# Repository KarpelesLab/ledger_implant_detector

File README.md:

# Ledger Implant Detector

> **⚠️ STATUS: PROTOTYPE, NOT VALIDATED**
>
> Rev 0.2 of the integrated board has been built (5 boards, 2026-11) and its blocks work, but it
> has a ~12 dB notch around 1.4 GHz that has to be fixed before it can run the detection rule.
> Rev 0.3 fixes the most likely cause and is generated but not built. The detection rule itself
> rests on **one genuine and one tampered Nano X**. Do not rely on this device to declare a wallet
> "clean" until it has been characterised on many more units and this banner has been removed.

| top: the cell | underside: the electronics |
|---|---|
|  |  |

A bench box for spotting **implanted antennas inside hardware wallets** (e.g. a Ledger). The target
threat is a supply-chain implant that adds a cellular (LTE) modem to the device: its antenna is a
resonant structure that a genuine unit doesn't have.

You slide the wallet into an open **TEM cell**, press a button, and read a screen and a green or red
LED. There's no VNA, no cables and no positioning skill involved. It is powered and updated over USB.

## How it detects

A TEM cell is a stripline big enough to put a wallet in: a flat metal plate (the septum) held 20 mm
above a ground plane, with tapered ramps at each end. It sets up a fairly uniform field over an
80 x 80 mm test area, so the result hardly depends on where the wallet lies.

The board sweeps a signal through the cell and measures how much comes out the other side (|S21|).
An implant antenna tuned to an LTE band absorbs energy at its resonance, which shows up as a narrow
notch in the sweep. Placement, the battery and the wallet's own electronics only change the sweep
broadly.

**The rule:** wallet sweep minus empty-cell sweep, minus a 200 MHz running median, then look in
1.0-1.45 GHz for a notch at least 0.45 dB deep and 10-60 MHz wide. If one is found, the user re-seats
the wallet and the box sweeps again; two notches within 15 MHz give red. No per-model reference
wallet is needed, if this holds up on more units.

On the NanoVNA captures of 2026-10-26 (`tools/tem_detect.py`, details in
[docs/rev02_integrated.md](docs/rev02_integrated.md#why-a-magnitude-only-sweep-is-enough)):

| | result |
|---|---|
| tampered Nano X, all placements and both orientations | 12 of 12 flagged, 0.79-1.02 dB at ~1171 MHz |
| genuine Nano X | 13 of 14 clean (at most 0.24 dB); one outlier that didn't repeat |
| re-seat and repeat | tampered 8 of 8 pairs, genuine 0 of 10 |

The implant antenna's own S11 confirms the feature: it resonates at 1156-1245 MHz depending on what
surrounds it ([data/rf/2026-11-02/notes.md](data/rf/2026-11-02/notes.md)).

The thresholds were chosen after looking at these captures, so they set a hardware target (a sweep of
800-1600 MHz in 5 MHz steps, at most 0.05 dB of noise per point) rather than proving the rule.

## What it will miss

- **Compact coil antennas**, such as Joe Grand's tampered Nano X (a hand-wound ~6 mm spiral). It is
  too small to couple to the cell's uniform field and isn't seen in simulation. The capacitive array of
  [rev 0.1](docs/rev01_capacitive.md) caught it in simulation through the shortened battery, but that
  array is not on the current board. **A green result does not rule this type out.**
- **Implants built to dodge the rule**: a low-Q antenna, or a resonance outside the band.
- **Anything unmeasured**: Stax, Nano S Plus, a genuine Flex.

## The board

Generated into `hardware/integrated/` by `tools/gen_integrated_sch.py` and
`tools/gen_integrated_pcb.py`. Full design notes, calibration, firmware security and the USB data
interface are in [docs/rev02_integrated.md](docs/rev02_integrated.md).

- **One board is both the cell floor and the electronics**, 200 x 216 mm, 4 layers
  (JLC04161H-7628). Its top copper is the cell's ground plane with the two 3 mm landing lines; every
  part is on the underside. RF crosses the board through fenced vias, so there are no cables.
- **Septum and ramps** are the fixture kit's `tem_plate` and `tem_ramp` boards, on 20 mm nylon spacers.
- **Signal chain:** ADF4351 synthesizer (35 MHz - 4.4 GHz) → 10 dB pad → cell → 6 dB pad → AD8318
  log detector → ADS1115 16-bit ADC.
- **Control:** Raspberry Pi Pico 2 module (RP2350), 2 inch ST7789 LCD, green and red LEDs, one button.
- **Hacks:** fit SMA J1/J2 and remove R1/R20 to use the cell with a NanoVNA; U.FL J5 on the
  synthesizer's second output; spare GPIO and ADC lines on J4; test points on the RF blocks.

Ordering steps: [hardware/integrated/ORDER.md](hardware/integrated/ORDER.md).

### Status

| rev | state |
|---|---|
| 0.2 | 5 boards built (JLC, 2026-11). Synthesizer, detector, ADC, LCD, LEDs and USB all work with the bring-up firmware. A ~12 dB notch near 1.4 GHz appears on both boards. Bench tests ruled out the cell, leakage and the detector's soldering, and point to long stubs on the synthesizer's RFOUTA- termination and the detector's INLO decoupling (not yet confirmed) |
| 0.3 | Generated, not built. Every ADF4351 and AD8318 support part is placed by hand at its pin, +5VA is a pour under the detector, and the router is kept out of sensitive areas. See [Rev 0.3](docs/rev02_integrated.md#rev-03-layout-fixes) |

### Firmware

`firmware/bringup` is **bring-up firmware**, not the detector: it gives raw sweeps and per-block
checks over USB serial, with no verdict and no stored reference. Build it with the Pico SDK:

```sh
cmake -S firmware/bringup -B build/bringup -G Ninja -DPICO_SDK_PATH=/path/to/pico-sdk
ninja -C build/bringup
```

Flash `build/bringup/lid_bringup.uf2` by holding BOOTSEL on the Pico while plugging it in, or send
`bootsel` to running firmware. Then use `tools/bringup.py` (Linux):

```sh
python3 tools/bringup.py cmd status               # any firmware command (try: help)
python3 tools/bringup.py sweep 1000 1450 5        # raw sweep, start/stop/step in MHz
python3 tools/bringup.py noise 1000 1450 5 -n 5   # per-point spread in dB (target <= 0.05 dB)
```

The detector firmware still has to be written: self-check, the rule, the green/red result, signed
updates and the HID interface for specialist data collection.

## How we got here

1. **Rev 0.1, capacitive array plus RF loop** ([docs/rev01_capacitive.md](docs/rev01_capacitive.md)):
   a handheld with eight capacitive electrodes and a near-field loop for a NanoVNA. Not built.
2. **Simulations** ([docs/simulation.md](docs/simulation.md)): floating antenna copper hidden behind
   the battery isn't detectable capacitively, but an RF probe sees a narrow in-band absorption that
   plain copper doesn't.
3. **First NanoVNA session** on a tampered Nano X
   ([data/rf/2026-10-18/notes.md](data/rf/2026-10-18/notes.md)): a resonance was visible, but only
   with the probe right over the antenna's feed.
4. **RF fixture kit** ([docs/fixtures.md](docs/fixtures.md), `hardware/fixtures/`): a slot line and an
   open TEM cell to remove that position dependence. On 2026-10-26 the TEM cell showed the tampered
   unit's notch at every placement ([data/rf/2026-10-26/notes.md](data/rf/2026-10-26/notes.md)).
   Crossed and coaxial large loops were simulated too, and the TEM cell stayed the practical choice.
5. **Integrated TEM cell** (rev 0.2, then 0.3): the fixture with the NanoVNA replaced by an on-board
   scalar sweep.

## Repository layout

```
hardware/
  integrated/   the integrated TEM cell (KiCad 10), fab/ has gerbers, JLC BOM/CPL, schematic PDF
  fixtures/     NanoVNA fixture kit: slot line, TEM base, septum plate, ramps
  detector/     rev 0.1 capacitive board (not built)
  lib/          project symbols and footprints
firmware/
  bringup/      rev 0.2 bring-up firmware (Pico SDK)
tools/          generators for every KiCad project, NanoVNA capture and analysis, bringup.py
sim/            electrostatic and FDTD simulations
data/rf/        NanoVNA captures with session notes
docs/           design notes, simulations, measurements, renders
```

## Regenerating

The KiCad files are generated by the scripts in `tools/`, so the design is reviewable as code. Treat
the committed `.kicad_pcb` as the source of truth: the router isn't deterministic, so regenerating
gives a different layout.

The integrated board needs KiCad 10 (its Python `pcbnew` module and `kicad-cli`), Java 17+ and
[Freerouting](https://github.com/freerouting/freerouting) 2.1.0:

```sh
cd tools
python3 gen_integrated_sch.py
FREEROUTING_JAR=/path/to/freerouting-2.1.0.jar \
    FREEROUTING_EXTRA="--gui.enabled=false --router.job_timeout=00:10:00" \
    python3 gen_integrated_pcb.py           # place, hand-route RF and support parts, autoroute, pour
python3 gen_integrated_pcb.py --outputs     # gerbers, BOM/CPL, schematic PDF, renders, DRC/ERC
```

It can leave a few connections open. Run several attempts with `LID_PCB_OUT` set to different paths
and keep one with 0 unconnected in DRC. The fixtures come from `tools/gen_fixtures.py`; the rev 0.1
board's steps are in [docs/rev01_capacitive.md](docs/rev01_capacitive.md#files-and-regenerating).

## License

Not yet chosen.

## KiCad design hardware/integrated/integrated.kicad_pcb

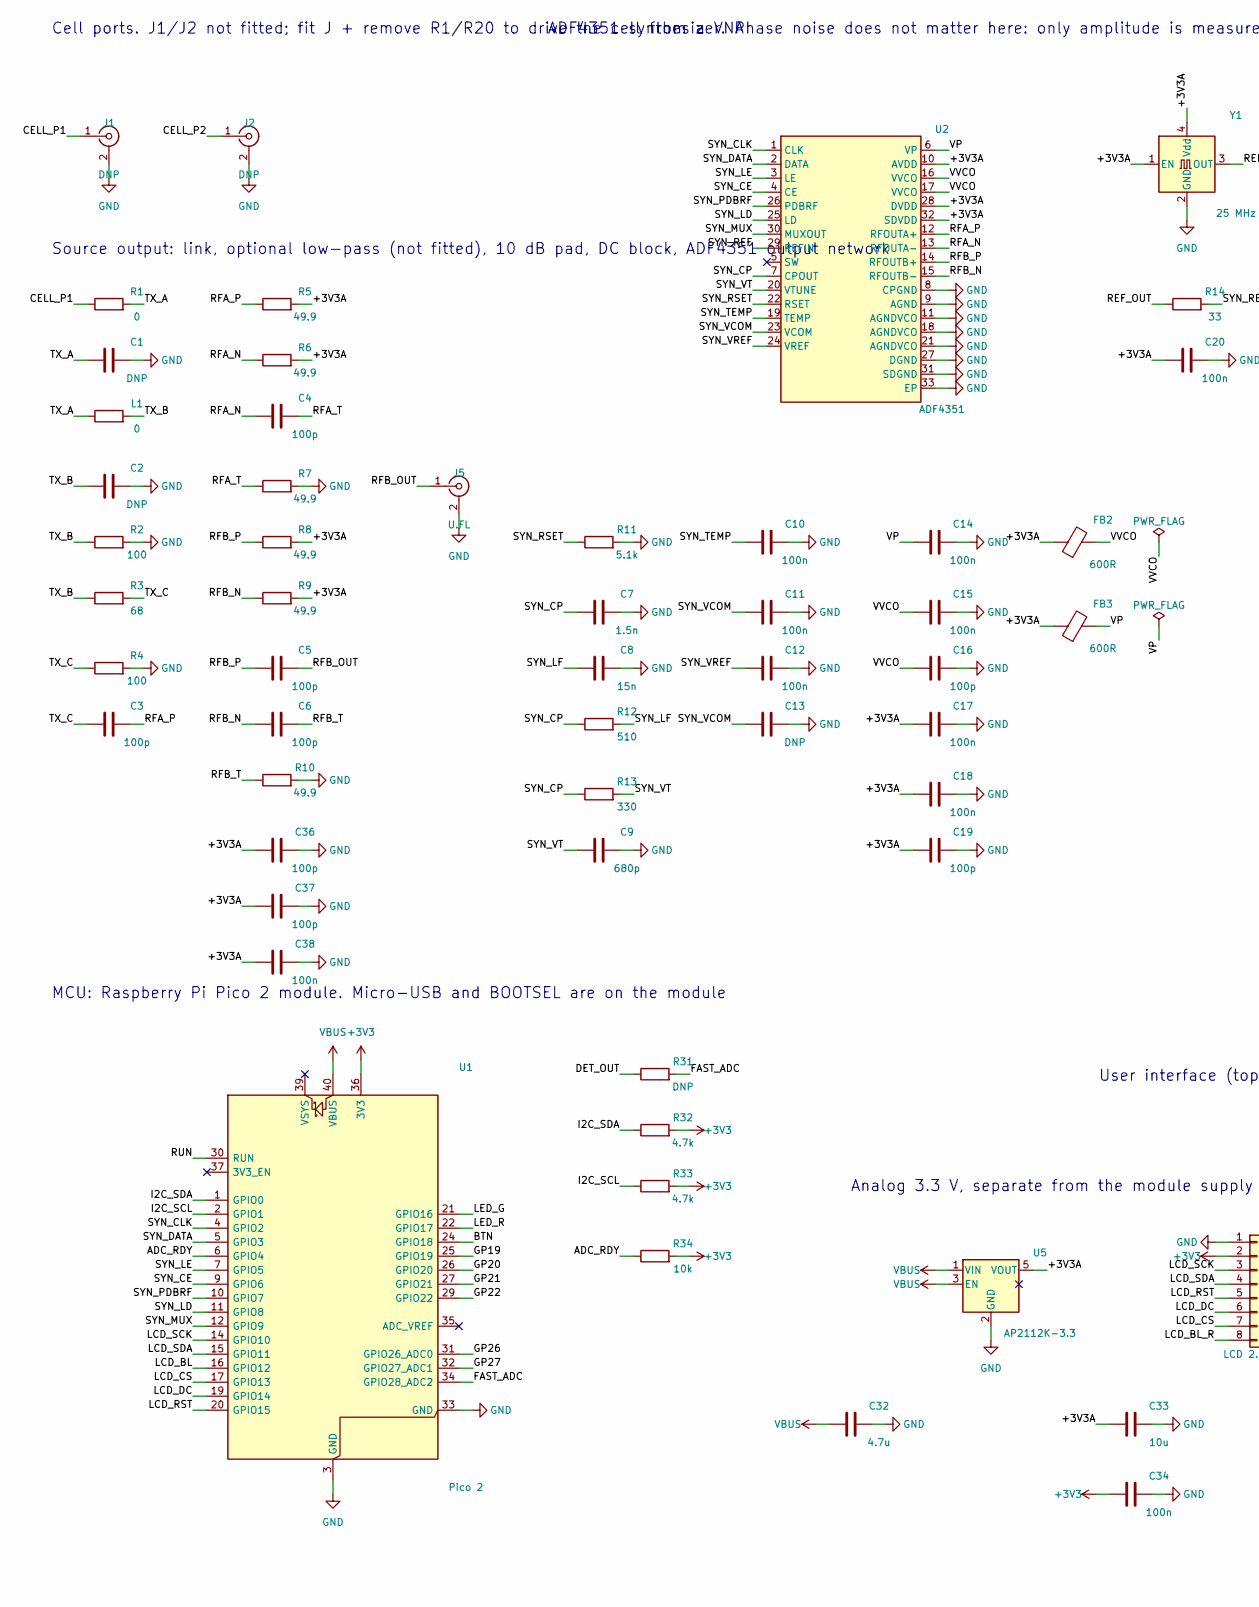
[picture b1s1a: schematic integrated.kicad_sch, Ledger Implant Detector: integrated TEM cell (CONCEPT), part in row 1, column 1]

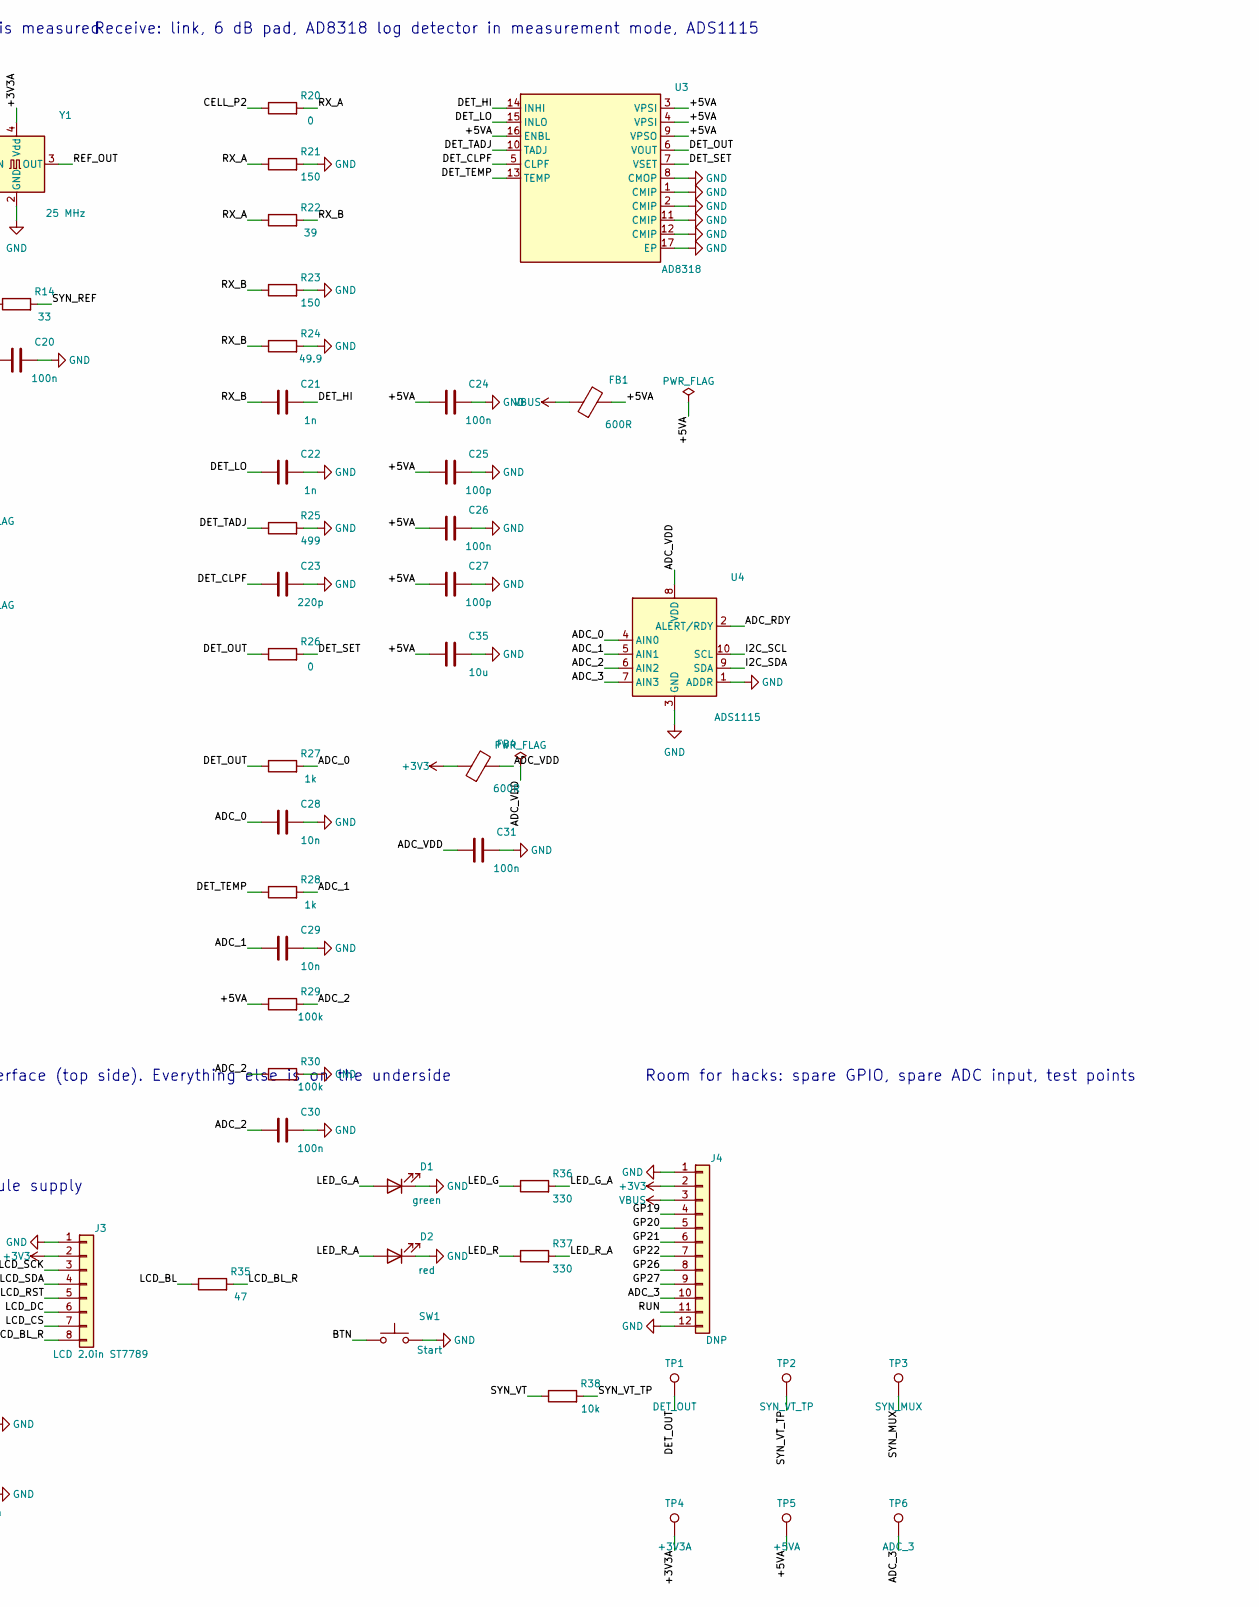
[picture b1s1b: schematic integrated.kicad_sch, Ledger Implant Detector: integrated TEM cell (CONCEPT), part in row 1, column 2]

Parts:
C1, C2, C13: DNP; C_0603_1608Metric
C3, C4, C5, C6, C16, C19, C25, C27, C36: 100p; C_0603_1608Metric
C7: 1.5n; C_0603_1608Metric
C8: 15n; C_0603_1608Metric
C9: 680p; C_0603_1608Metric
C10, C11, C12, C14, C15, C17, C18, C20, C24, C26, C30, C31, C34: 100n; C_0603_1608Metric
C21, C22: 1n; C_0603_1608Metric
C23: 220p; C_0603_1608Metric
C28, C29: 10n; C_0603_1608Metric
C32: 4.7u; C_0805_2012Metric; Voltage 10V
C33, C35: 10u; C_0805_2012Metric; Voltage 10V
C37: 100p; C_0402_1005Metric
C38: 100n; C_0402_1005Metric
D1: green; LED_D5.0mm
D2: red; LED_D5.0mm
FB1, FB2, FB3, FB4: 600R; L_0603_1608Metric
J1, J2: DNP; SMA_Samtec_SMA-J-P-H-ST-EM1_EdgeMount
J3: LCD 2.0in ST7789; PinHeader_1x08_P2.54mm_Vertical
J4: DNP; PinHeader_1x12_P2.54mm_Vertical
J5: U.FL; U.FL_Hirose_U.FL-R-SMT-1_Vertical; MPN U.FL-R-SMT-1(80); LCSC C88374
L1: 0; R_0603_1608Metric
R1, R20, R26: 0; R_0603_1608Metric
R2, R4: 100; R_0603_1608Metric
R3: 68; R_0603_1608Metric
R5, R6, R7, R8, R9, R10, R24: 49.9; R_0603_1608Metric
R11: 5.1k; R_0603_1608Metric
R12: 510; R_0603_1608Metric
R13, R36, R37: 330; R_0603_1608Metric
R14: 33; R_0603_1608Metric
R21, R23: 150; R_0603_1608Metric
R22: 39; R_0603_1608Metric
R25: 499; R_0603_1608Metric
R27, R28: 1k; R_0603_1608Metric
R29, R30: 100k; R_0603_1608Metric
R31: DNP; R_0603_1608Metric
R32, R33: 4.7k; R_0603_1608Metric
R34, R38: 10k; R_0603_1608Metric
R35: 47; R_0603_1608Metric
SW1: Start; SW_PUSH_6mm
TP1: DET_OUT; TestPoint_Pad_D1.5mm
TP2: SYN_VT_TP; TestPoint_Pad_D1.5mm
TP3: SYN_MUX; TestPoint_Pad_D1.5mm
TP4: +3V3A; TestPoint_Pad_D1.5mm
TP5: +5VA; TestPoint_Pad_D1.5mm
TP6: ADC_3; TestPoint_Pad_D1.5mm
U1: Pico 2; RaspberryPi_Pico_Common_THT; MPN SC1631
U2: ADF4351; QFN-32-1EP_5x5mm_P0.5mm_EP3.45x3.45mm; MPN ADF4351BCPZ
U3: AD8318; Analog_LFCSP-16-1EP_4x4mm_P0.65mm_EP2.35x2.35mm; MPN AD8318ACPZ-REEL7
U4: ADS1115; TSSOP-10_3x3mm_P0.5mm; MPN ADS1115IDGSR
U5: AP2112K-3.3; SOT-23-5; MPN AP2112K-3.3TRG1
Y1: 25 MHz; Oscillator_SMD_Abracon_ASE-4Pin_3.2x2.5mm; MPN OT322525MJBA4SL; LCSC C669088

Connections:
+3V3: C34.1, FB4.1, J3.2, J4.2, R32.2, R33.2, R34.2, U1.36 (3V3)
/+3V3A: C17.1, C18.1, C19.1, C20.1, C33.1, C36.1, C37.1, C38.1, FB2.1, FB3.1, R5.2, R6.2, R8.2, R9.2, TP4.1, U2.10 (AVDD), U2.28 (DVDD), U2.32 (SDVDD), U5.5 (VOUT), Y1.1 (EN), Y1.4 (Vdd)
/ADC_0: C28.1, R27.2, U4.4 (AIN0)
/ADC_1: C29.1, R28.2, U4.5 (AIN1)
/ADC_2: C30.1, R29.2, R30.1, U4.6 (AIN2)
/ADC_3: J4.10, TP6.1, U4.7 (AIN3)
/ADC_RDY: R34.1, U1.6 (GPIO4), U4.2 (ALERT/RDY)
/BTN: SW1.1, U1.24 (GPIO18)
/CELL_P1: J1.1 (In), R1.1
/CELL_P2: J2.1 (In), R20.1
/DET_CLPF: C23.1, U3.5 (CLPF)
/DET_HI: C21.2, U3.14 (INHI)
/DET_LO: C22.1, U3.15 (INLO)
/DET_OUT: R26.1, R27.1, R31.1, TP1.1, U3.6 (VOUT)
/DET_SET: R26.2, U3.7 (VSET)
/DET_TADJ: R25.1, U3.10 (TADJ)
/DET_TEMP: R28.1, U3.13 (TEMP)
/FAST_ADC: R31.2, U1.34 (GPIO28_ADC2)
/GP19: J4.4, U1.25 (GPIO19)
/GP20: J4.5, U1.26 (GPIO20)
/GP21: J4.6, U1.27 (GPIO21)
/GP22: J4.7, U1.29 (GPIO22)
/GP26: J4.8, U1.31 (GPIO26_ADC0)
/GP27: J4.9, U1.32 (GPIO27_ADC1)
/I2C_SCL: R33.1, U1.2 (GPIO1), U4.10 (SCL)
/I2C_SDA: R32.1, U1.1 (GPIO0), U4.9 (SDA)
/LCD_BL: R35.1, U1.16 (GPIO12)
/LCD_BL_R: J3.8, R35.2
/LCD_CS: J3.7, U1.17 (GPIO13)
/LCD_DC: J3.6, U1.19 (GPIO14)
/LCD_RST: J3.5, U1.20 (GPIO15)
/LCD_SCK: J3.3, U1.14 (GPIO10)
/LCD_SDA: J3.4, U1.15 (GPIO11)
/LED_G: R36.1, U1.21 (GPIO16)
/LED_G_A: D1.2 (A), R36.2
/LED_R: R37.1, U1.22 (GPIO17)
/LED_R_A: D2.2 (A), R37.2
/REF_OUT: R14.1, Y1.3 (OUT)
/RFA_N: C4.1, R6.1, U2.13 (RFOUTA-)
/RFA_P: C3.2, R5.1, U2.12 (RFOUTA+)
/RFA_T: C4.2, R7.1
/RFB_N: C6.1, R9.1, U2.15 (RFOUTB-)
/RFB_OUT: C5.2, J5.1 (In)
/RFB_P: C5.1, R8.1, U2.14 (RFOUTB+)
/RFB_T: C6.2, R10.1
/RUN: J4.11, U1.30 (RUN)
/RX_A: R20.2, R21.1, R22.1
/RX_B: C21.1, R22.2, R23.1, R24.1
/SYN_CE: U1.9 (GPIO6), U2.4 (CE)
/SYN_CLK: U1.4 (GPIO2), U2.1 (CLK)
/SYN_CP: C7.1, R12.1, R13.1, U2.7 (CPOUT)
/SYN_DATA: U1.5 (GPIO3), U2.2 (DATA)
/SYN_LD: U1.11 (GPIO8), U2.25 (LD)
/SYN_LE: U1.7 (GPIO5), U2.3 (LE)
/SYN_LF: C8.1, R12.2
/SYN_MUX: TP3.1, U1.12 (GPIO9), U2.30 (MUXOUT)
/SYN_PDBRF: U1.10 (GPIO7), U2.26 (PDBRF)
/SYN_REF: R14.2, U2.29 (REFIN)
/SYN_RSET: R11.1, U2.22 (RSET)
/SYN_TEMP: C10.1, U2.19 (TEMP)
/SYN_VCOM: C11.1, C13.1, U2.23 (VCOM)
/SYN_VREF: C12.1, U2.24 (VREF)
/SYN_VT: C9.1, R13.2, R38.1, U2.20 (VTUNE)
/SYN_VT_TP: R38.2, TP2.1
/TX_A: C1.1, L1.1, R1.2
/TX_B: C2.1, L1.2, R2.1, R3.1
/TX_C: C3.1, R3.2, R4.1
GND: C1.2, C2.2, C7.2, C8.2, C9.2, C10.2, C11.2, C12.2, C13.2, C14.2, C15.2, C16.2, C17.2, C18.2, C19.2, C20.2, C22.2, C23.2, C24.2, C25.2, C26.2, C27.2, C28.2, C29.2, C30.2, C31.2, C32.2, C33.2, C34.2, C35.2, C36.2, C37.2, C38.2, D1.1 (K), D2.1 (K), J1.2 (Ext), J2.2 (Ext), J3.1, J4.1, J4.12, J5.2 (Ext), R2.2, R4.2, R7.2, R10.2, R11.2, R21.2, R23.2, R24.2, R25.2, R30.2, SW1.2, U1.3 (GND), U1.8 (GND), U1.13 (GND), U1.18 (GND), U1.23 (GND), U1.28 (GND), U1.33 (AGND), U1.38 (GND), U2.8 (CPGND), U2.9 (AGND), U2.11 (AGNDVCO), U2.18 (AGNDVCO), U2.21 (AGNDVCO), U2.27 (DGND), U2.31 (SDGND), U2.33 (EP), U3.1 (CMIP), U3.2 (CMIP), U3.8 (CMOP), U3.11 (CMIP), U3.12 (CMIP), U3.17 (EP), U4.1 (ADDR), U4.3 (GND), U5.2 (GND), Y1.2 (GND)
VBUS: C32.1, FB1.1, J4.3, U1.40 (VBUS), U5.1 (VIN), U5.3 (EN)

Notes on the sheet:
Cell ports. J1/J2 not fitted; fit J + remove R1/R20 to drive the cell from a VNA
Source output: link, optional low-pass (not fitted), 10 dB pad, DC block, ADF4351 output network
ADF4351 synthesizer. Phase noise does not matter here: only amplitude is measured
Receive: link, 6 dB pad, AD8318 log detector in measurement mode, ADS1115
MCU: Raspberry Pi Pico 2 module. Micro-USB and BOOTSEL are on the module
Analog 3.3 V, separate from the module supply
User interface (top side). Everything else is on the underside
Room for hacks: spare GPIO, spare ADC input, test points

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
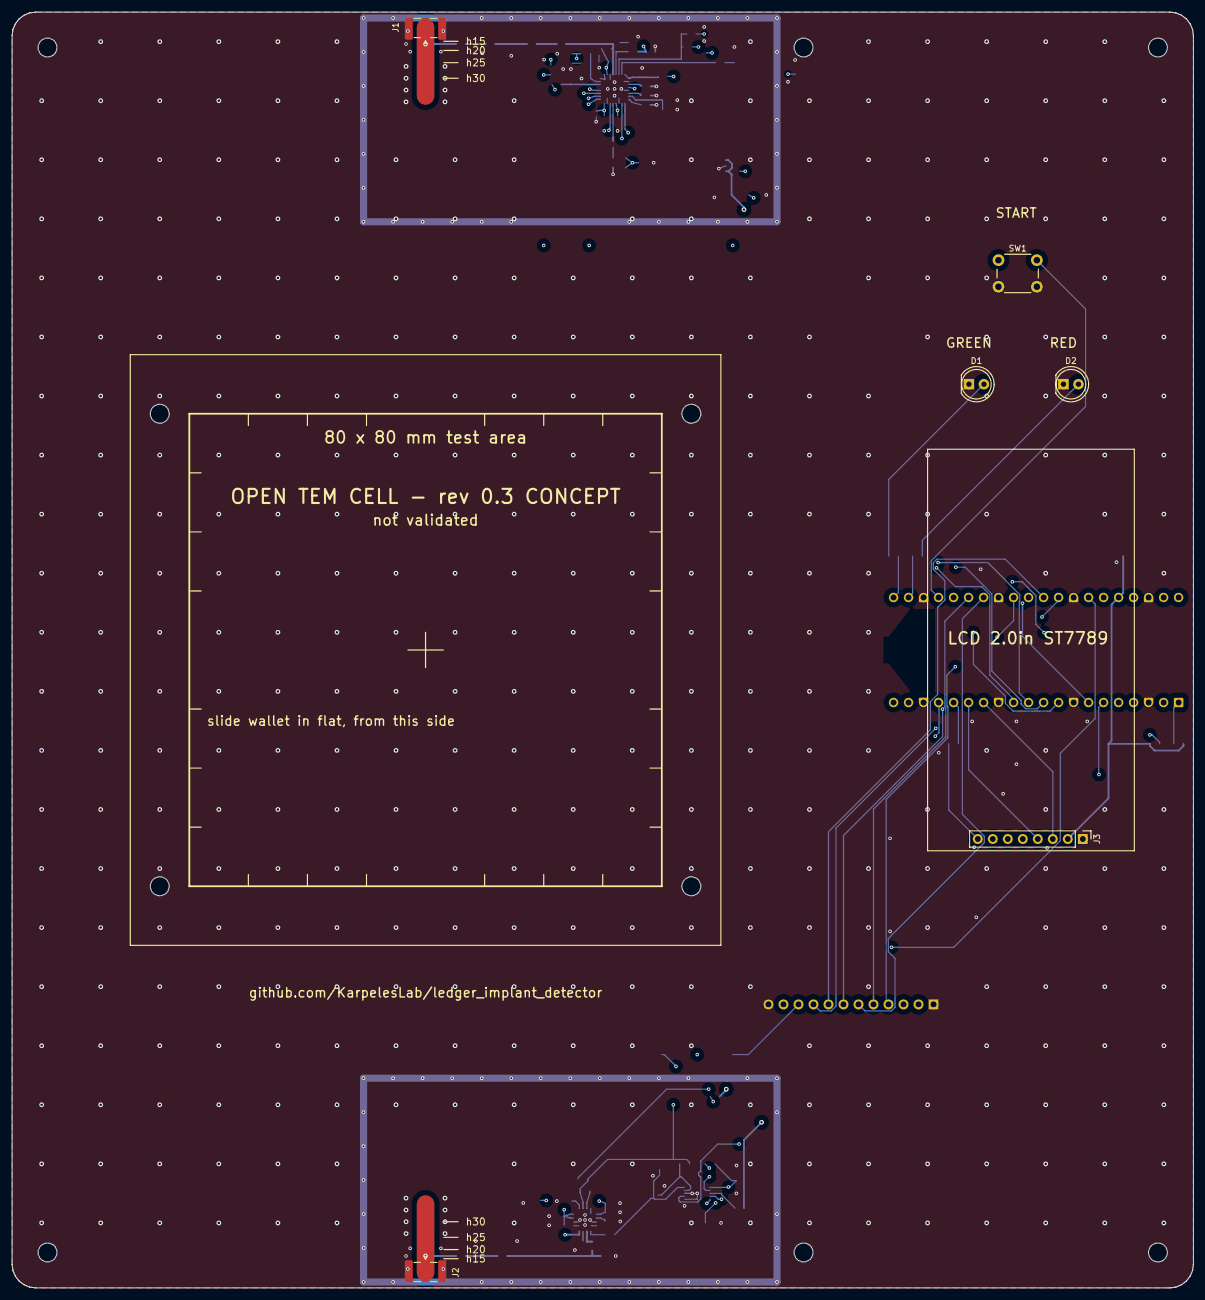
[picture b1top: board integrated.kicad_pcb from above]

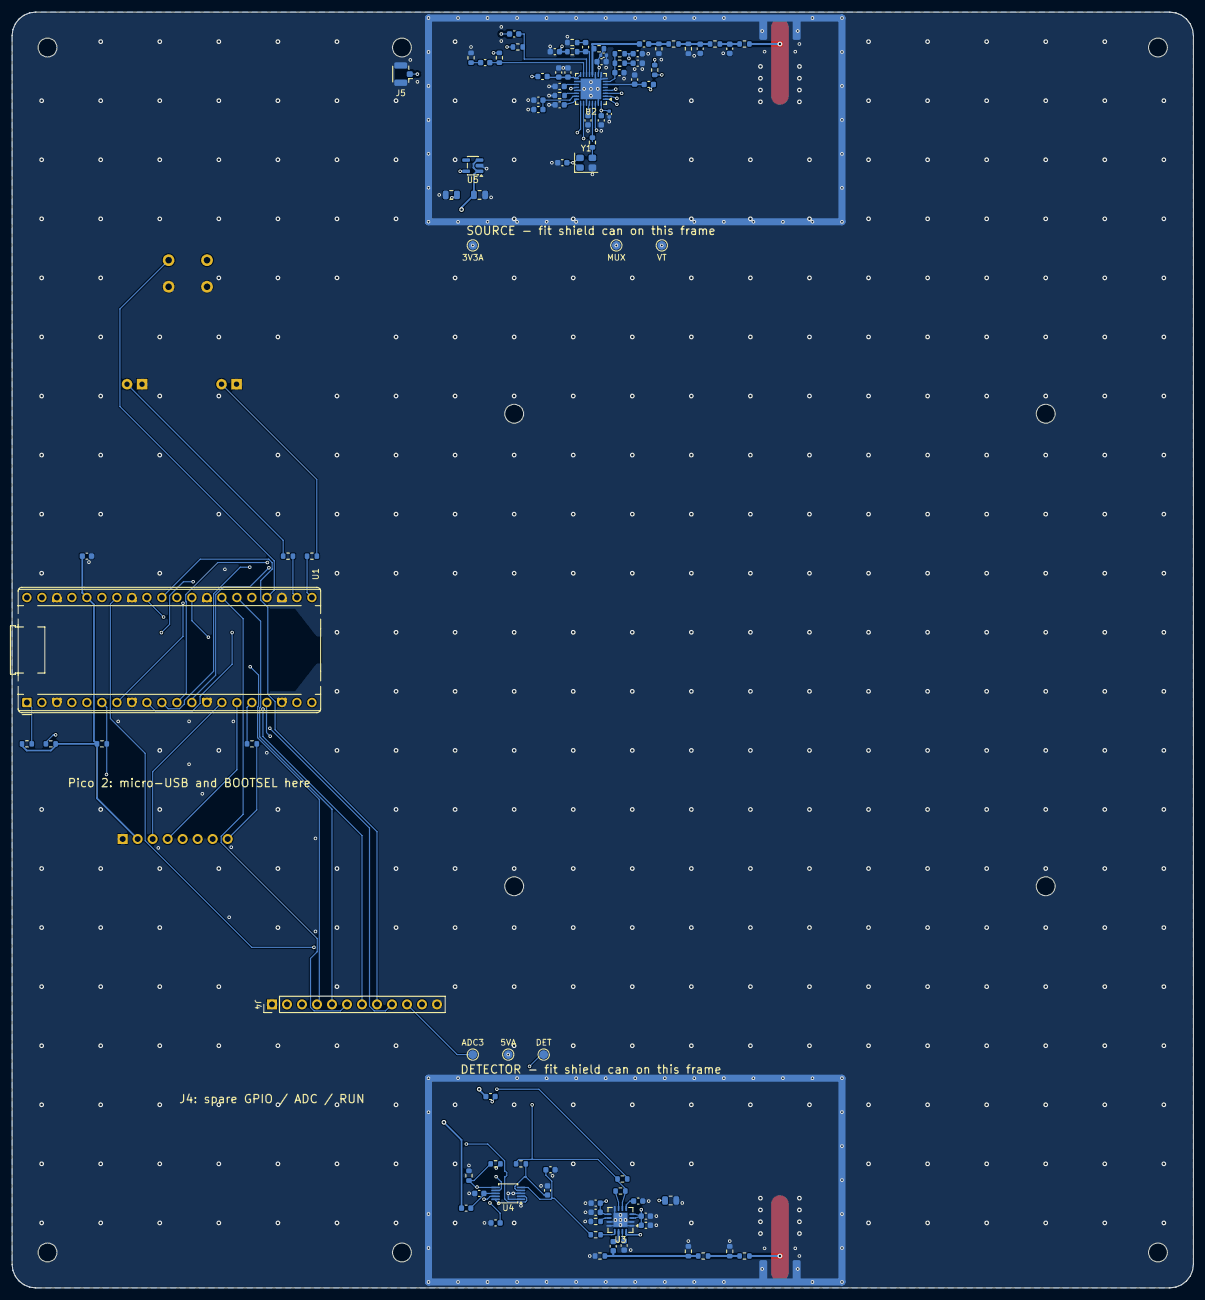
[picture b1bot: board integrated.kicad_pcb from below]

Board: 4 copper layers, 200.0 x 216.0 mm, 106 parts (90 on the bottom side), 73 nets.

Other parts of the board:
H1, H2, H3, H4, H5, H6, H7, H8, H9, H10: MountingHole_3.2mm_M3

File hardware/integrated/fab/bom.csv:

"Designator","Value","Footprint","MPN","Manufacturer","LCSC","Qty","DNP"
"C3-C6,C16,C19,C25,C27,C36","100p","Capacitor_SMD:C_0603_1608Metric","","","","9",""
"C7","1.5n","Capacitor_SMD:C_0603_1608Metric","","","","1",""
"C8","15n","Capacitor_SMD:C_0603_1608Metric","","","","1",""
"C9","680p","Capacitor_SMD:C_0603_1608Metric","","","","1",""
"C10-C12,C14,C15,C17,C18,C20,C24,C26,C30,C31,C34","100n","Capacitor_SMD:C_0603_1608Metric","","","","13",""
"C21,C22","1n","Capacitor_SMD:C_0603_1608Metric","","","","2",""
"C23","220p","Capacitor_SMD:C_0603_1608Metric","","","","1",""
"C28,C29","10n","Capacitor_SMD:C_0603_1608Metric","","","","2",""
"C32","4.7u","Capacitor_SMD:C_0805_2012Metric","","","","1",""
"C33,C35","10u","Capacitor_SMD:C_0805_2012Metric","","","","2",""
"C37","100p","Capacitor_SMD:C_0402_1005Metric","","","","1",""
"C38","100n","Capacitor_SMD:C_0402_1005Metric","","","","1",""
"D1","green","LED_THT:LED_D5.0mm","","","","1",""
"D2","red","LED_THT:LED_D5.0mm","","","","1",""
"FB1-FB4","600R","Inductor_SMD:L_0603_1608Metric","","","","4",""
"J3","LCD 2.0in ST7789","Connector_PinHeader_2.54mm:PinHeader_1x08_P2.54mm_Vertical","","","","1",""
"J5","U.FL","Connector_Coaxial:U.FL_Hirose_U.FL-R-SMT-1_Vertical","U.FL-R-SMT-1(80)","","C88374","1",""
"L1,R1,R20,R26","0","Resistor_SMD:R_0603_1608Metric","","","","4",""
"R2,R4","100","Resistor_SMD:R_0603_1608Metric","","","","2",""
"R3","68","Resistor_SMD:R_0603_1608Metric","","","","1",""
"R5-R10,R24","49.9","Resistor_SMD:R_0603_1608Metric","","","","7",""
"R11","5.1k","Resistor_SMD:R_0603_1608Metric","","","","1",""
"R12","510","Resistor_SMD:R_0603_1608Metric","","","","1",""
"R13,R36,R37","330","Resistor_SMD:R_0603_1608Metric","","","","3",""
"R14","33","Resistor_SMD:R_0603_1608Metric","","","","1",""
"R21,R23","150","Resistor_SMD:R_0603_1608Metric","","","","2",""
"R22","39","Resistor_SMD:R_0603_1608Metric","","","","1",""
"R25","499","Resistor_SMD:R_0603_1608Metric","","","","1",""
"R27,R28","1k","Resistor_SMD:R_0603_1608Metric","","","","2",""
"R29,R30","100k","Resistor_SMD:R_0603_1608Metric","","","","2",""
"R32,R33","4.7k","Resistor_SMD:R_0603_1608Metric","","","","2",""
"R34,R38","10k","Resistor_SMD:R_0603_1608Metric","","","","2",""
"R35","47","Resistor_SMD:R_0603_1608Metric","","","","1",""
"SW1","Start","Button_Switch_THT:SW_PUSH_6mm","","","","1",""
"U1","Pico 2","Module:RaspberryPi_Pico_Common_THT","SC1631","Raspberry Pi","","1",""
"U2","ADF4351","Package_DFN_QFN:QFN-32-1EP_5x5mm_P0.5mm_EP3.45x3.45mm","ADF4351BCPZ","Analog Devices","","1",""
"U3","AD8318","Package_CSP:Analog_LFCSP-16-1EP_4x4mm_P0.65mm_EP2.35x2.35mm","AD8318ACPZ-REEL7","Analog Devices","","1",""
"U4","ADS1115","Package_SO:TSSOP-10_3x3mm_P0.5mm","ADS1115IDGSR","Texas Instruments","","1",""
"U5","AP2112K-3.3","Package_TO_SOT_SMD:SOT-23-5","AP2112K-3.3TRG1","Diodes Inc","","1",""
"Y1","25 MHz","Oscillator:Oscillator_SMD_Abracon_ASE-4Pin_3.2x2.5mm","OT322525MJBA4SL","YXC","C669088","1",""

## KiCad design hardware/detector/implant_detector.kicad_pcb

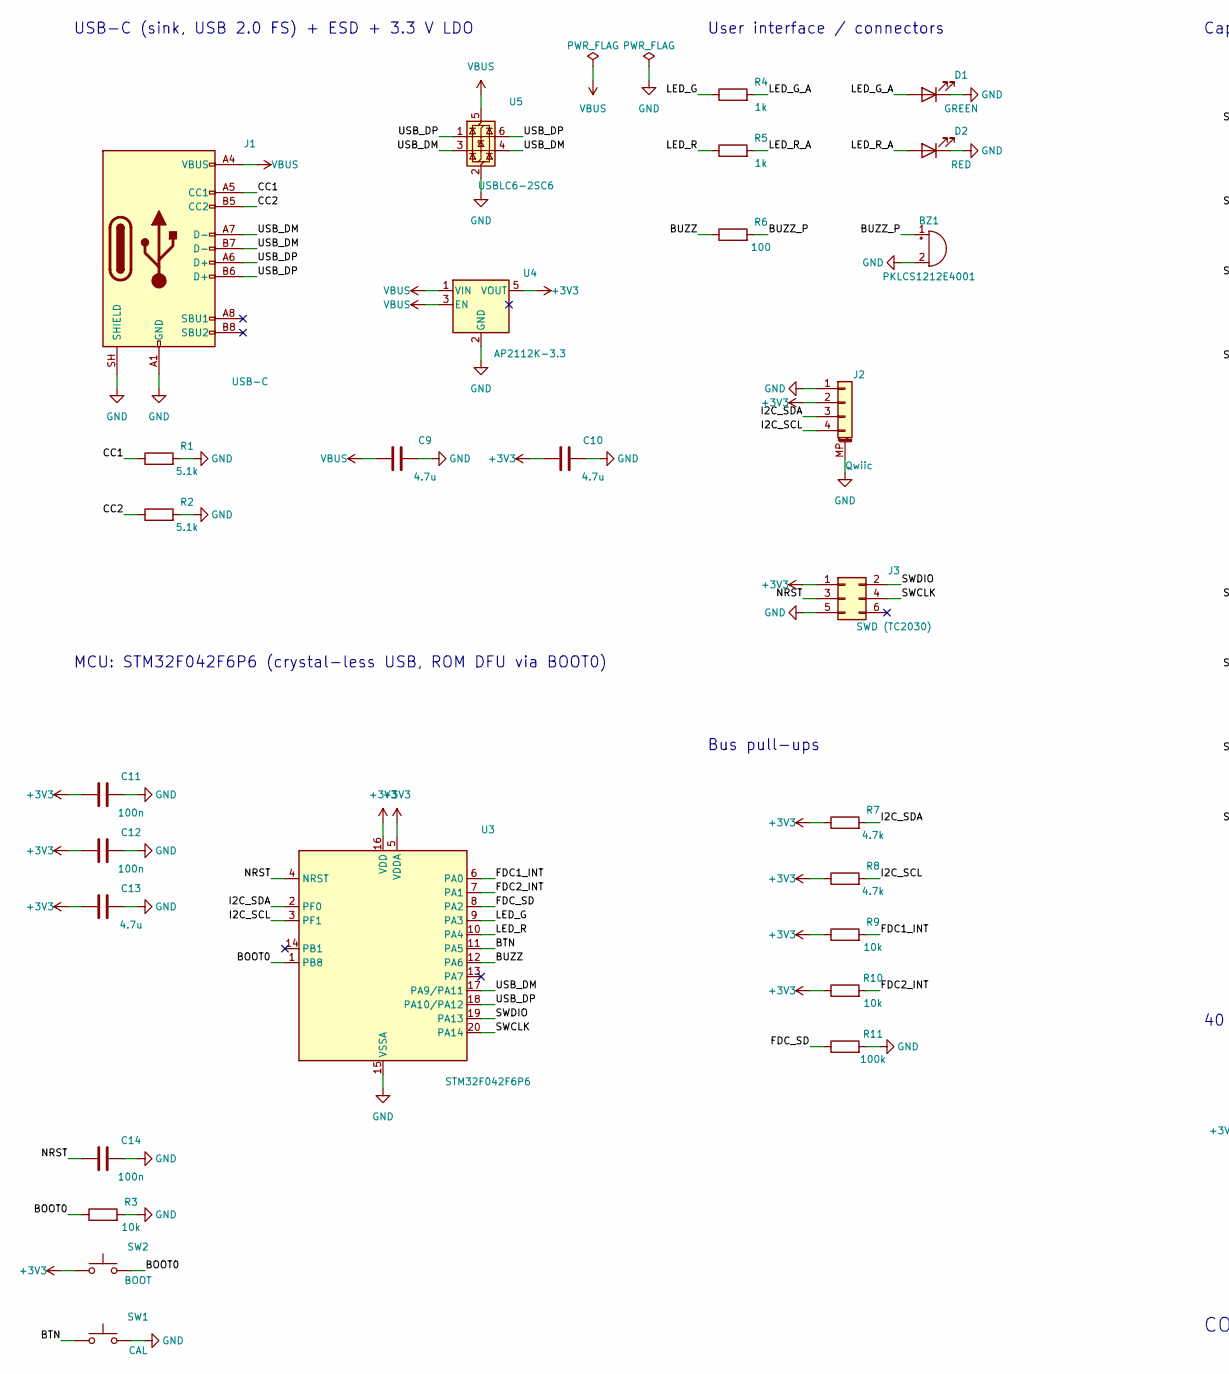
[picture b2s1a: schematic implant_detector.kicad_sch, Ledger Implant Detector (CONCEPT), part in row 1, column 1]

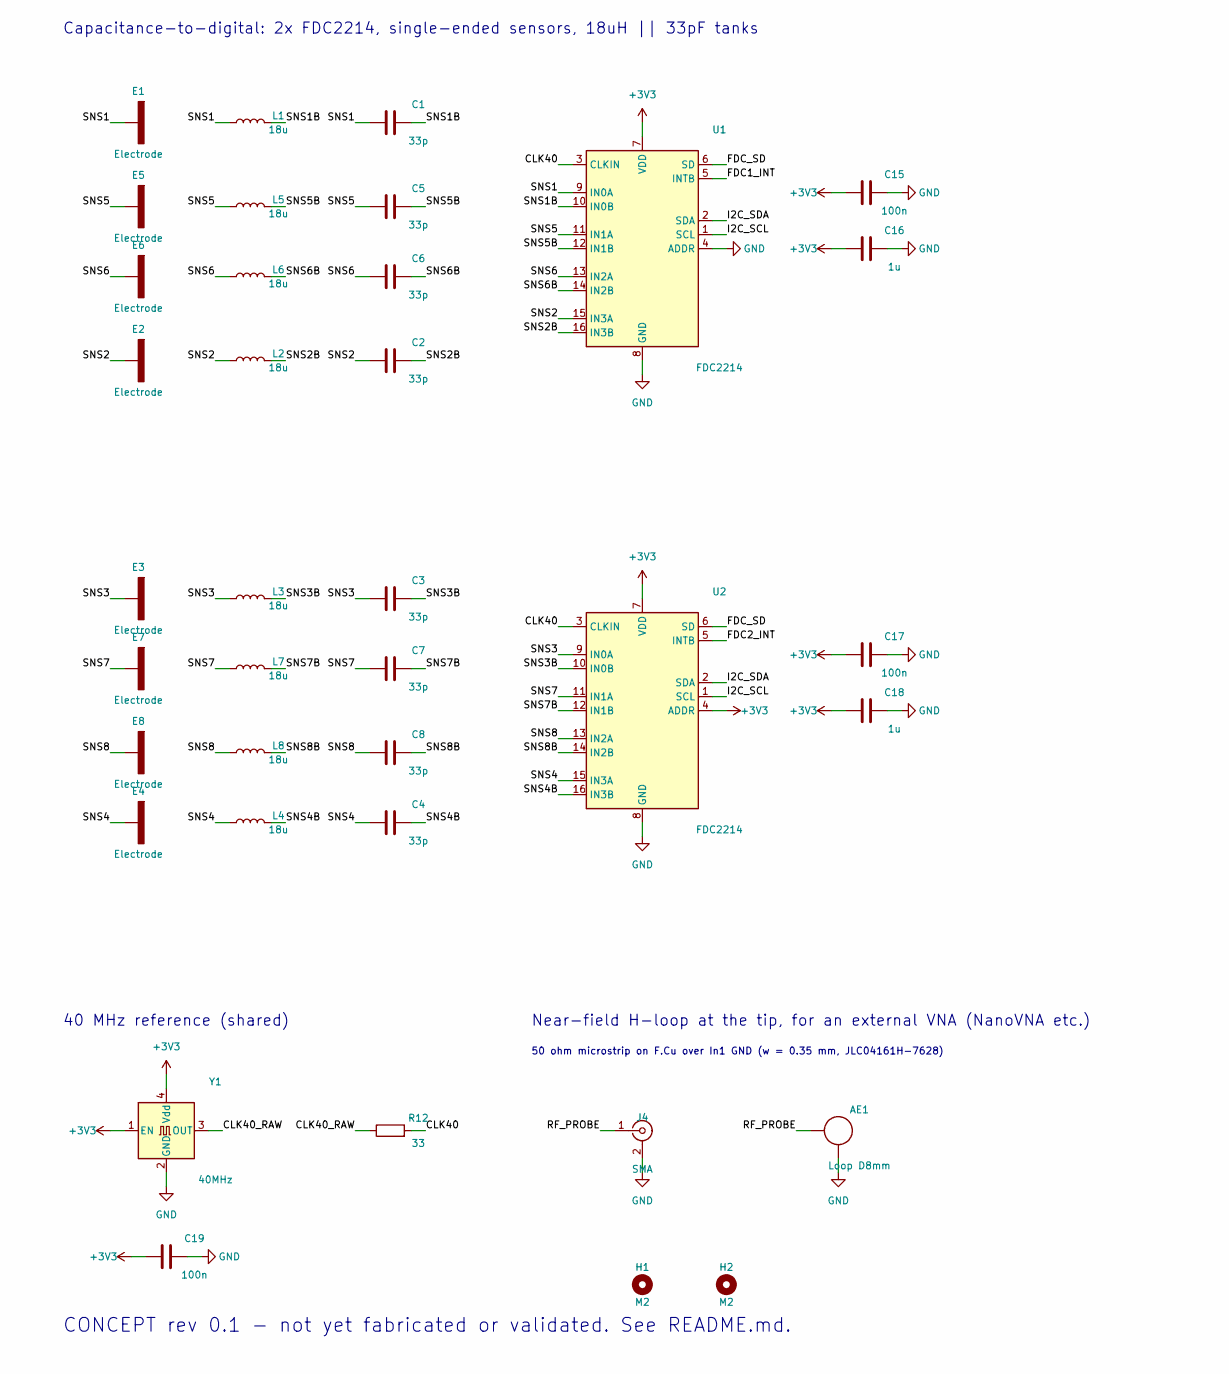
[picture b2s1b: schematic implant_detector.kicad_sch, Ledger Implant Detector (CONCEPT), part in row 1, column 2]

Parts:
AE1: Loop D8mm; NearField_Loop_D8mm
BZ1: PKLCS1212E4001; Buzzer_Murata_PKLCS1212E; MPN PKLCS1212E4001-R1
C1, C2, C3, C4, C5, C6, C7, C8: 33p; C_0603_1608Metric; Tolerance 1%; MPN GRM1885C1H330FA01D
C9, C10, C13: 4.7u; C_0603_1608Metric; Voltage 10V
C11, C12, C14, C15, C17, C19: 100n; C_0603_1608Metric
C16, C18: 1u; C_0603_1608Metric
D1: GREEN; LED_0603_1608Metric; MPN 19-217/GHC-YR1S2/3T
D2: RED; LED_0603_1608Metric; MPN 19-217/R6C-AL1M2VY/3T
E1, E2, E3, E4, E5, E6, E7, E8: Electrode; Electrode_14x14mm
H1, H2: M2; MountingHole_2.2mm_M2
J1: USB-C; USB_C_Receptacle_HRO_TYPE-C-31-M-12; MPN TYPE-C-31-M-12; LCSC C165948
J2: Qwiic; JST_SH_SM04B-SRSS-TB_1x04-1MP_P1.00mm_Horizontal; MPN SM04B-SRSS-TB(LF)(SN)
J3: SWD (TC2030); Tag-Connect_TC2030-IDC-NL_2x03_P1.27mm_Vertical
J4: SMA; SMA_Samtec_SMA-J-P-H-ST-EM1_EdgeMount; MPN SMA-J-P-H-ST-EM1
L1, L2, L3, L4, L5, L6, L7, L8: 18u; L_1210_3225Metric; MPN CMH322522-180KL
R1, R2: 5.1k; R_0603_1608Metric
R3, R9, R10: 10k; R_0603_1608Metric
R4, R5: 1k; R_0603_1608Metric
R6: 100; R_0603_1608Metric
R7, R8: 4.7k; R_0603_1608Metric
R11: 100k; R_0603_1608Metric
R12: 33; R_0603_1608Metric
SW1: CAL; SW_SPST_PTS810; MPN PTS810 SJM 250 SMTR LFS
SW2: BOOT; SW_SPST_PTS810; MPN PTS810 SJM 250 SMTR LFS
U1, U2: FDC2214; WQFN-16-1EP_4x4mm_P0.5mm_EP2.6x2.6mm; MPN FDC2214RGHR
U3: STM32F042F6P6; TSSOP-20_4.4x6.5mm_P0.65mm; MPN STM32F042F6P6
U4: AP2112K-3.3; SOT-23-5; MPN AP2112K-3.3TRG1
U5: USBLC6-2SC6; SOT-23-6; MPN USBLC6-2SC6
Y1: 40MHz; Oscillator_SMD_Abracon_ASE-4Pin_3.2x2.5mm; MPN ASE-40.000MHZ-LC-T

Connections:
+3V3: C10.1, C11.1, C12.1, C13.1, C15.1, C16.1, C17.1, C18.1, C19.1, J2.2, J3.1, R7.1, R8.1, R9.1, R10.1, SW2.1, U1.7 (VDD), U2.4 (ADDR), U2.7 (VDD), U3.5 (VDDA), U3.16 (VDD), U4.5 (VOUT), Y1.1 (EN), Y1.4 (Vdd)
/BOOT0: R3.1, SW2.2, U3.1 (PB8)
/BTN: SW1.1, U3.11 (PA5)
/BUZZ: R6.1, U3.12 (PA6)
/BUZZ_P: BZ1.1 (+), R6.2
/CC1: J1.A5 (CC1), R1.1
/CC2: J1.B5 (CC2), R2.1
/CLK40: R12.2, U1.3 (CLKIN), U2.3 (CLKIN)
/CLK40_RAW: R12.1, Y1.3 (OUT)
/FDC1_INT: R9.2, U1.5 (INTB), U3.6 (PA0)
/FDC2_INT: R10.2, U2.5 (INTB), U3.7 (PA1)
/FDC_SD: R11.1, U1.6 (SD), U2.6 (SD), U3.8 (PA2)
/I2C_SCL: J2.4, R8.2, U1.1 (SCL), U2.1 (SCL), U3.3 (PF1)
/I2C_SDA: J2.3, R7.2, U1.2 (SDA), U2.2 (SDA), U3.2 (PF0)
/LED_G: R4.1, U3.9 (PA3)
/LED_G_A: D1.2 (A), R4.2
/LED_R: R5.1, U3.10 (PA4)
/LED_R_A: D2.2 (A), R5.2
/NRST: C14.1, J3.3, U3.4 (NRST)
/RF_PROBE: AE1.1 (FEED), J4.1 (In)
/SNS1: C1.1, E1.1, L1.1, U1.9 (IN0A)
/SNS1B: C1.2, L1.2, U1.10 (IN0B)
/SNS2: C2.1, E2.1, L2.1, U1.15 (IN3A)
/SNS2B: C2.2, L2.2, U1.16 (IN3B)
/SNS3: C3.1, E3.1, L3.1, U2.9 (IN0A)
/SNS3B: C3.2, L3.2, U2.10 (IN0B)
/SNS4: C4.1, E4.1, L4.1, U2.15 (IN3A)
/SNS4B: C4.2, L4.2, U2.16 (IN3B)
/SNS5: C5.1, E5.1, L5.1, U1.11 (IN1A)
/SNS5B: C5.2, L5.2, U1.12 (IN1B)
/SNS6: C6.1, E6.1, L6.1, U1.13 (IN2A)
/SNS6B: C6.2, L6.2, U1.14 (IN2B)
/SNS7: C7.1, E7.1, L7.1, U2.11 (IN1A)
/SNS7B: C7.2, L7.2, U2.12 (IN1B)
/SNS8: C8.1, E8.1, L8.1, U2.13 (IN2A)
/SNS8B: C8.2, L8.2, U2.14 (IN2B)
/SWCLK: J3.4, U3.20 (PA14)
/SWDIO: J3.2, U3.19 (PA13)
/USB_DM: J1.A7 (D-), J1.B7 (D-), U3.17 (PA9/PA11), U5.3 (I/O2), U5.4 (I/O2)
/USB_DP: J1.A6 (D+), J1.B6 (D+), U3.18 (PA10/PA12), U5.1 (I/O1), U5.6 (I/O1)

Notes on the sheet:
USB-C (sink, USB 2.0 FS) + ESD + 3.3 V LDO
MCU: STM32F042F6P6 (crystal-less USB, ROM DFU via BOOT0)
User interface / connectors
Bus pull-ups
40 MHz reference (shared)
Capacitance-to-digital: 2x FDC2214, single-ended sensors, 18uH || 33pF tanks
Near-field H-loop at the tip, for an external VNA (NanoVNA etc.)
50 ohm microstrip on F.Cu over In1 GND (w = 0.35 mm, JLC04161H-7628)
CONCEPT rev 0.1 - not yet fabricated or validated. See README.md.

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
